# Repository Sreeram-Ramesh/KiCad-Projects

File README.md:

# KiCad Projects

An archive for all my KiCad project folders for various projects I've been working on. Find more about each of these KiCad projects on their respective repos if they exist wherein I have shared about the project itself, here's a quick overview of my KiCad designs.

<br>

## Overview

Several attempts were made by me in the past to try out designing and printing PCBs for my personal high school projects. After constant yapping and getting my dad on-board for my PCB fab through JLC PCB, results were pretty bad cuz of my PCB design skills. Some pictures for context. Fast forwarding now, I understood high-school me was pretty dumb, or always that has been the case and I am living in delulu.

<br>

<p align="center">
&nbsp;

</p>

<br>

With all that being said here are some of my recent projects.

### [1. 555 ID Badge](https://www.youtube.com/playlist?list=PLEBQazB0HUyR24ckSZ5u05TZHV9khgA1O)

This project served as a great introduction for me in KiCad. I am grateful to Digikey and Shawn Hymel for their open-source project (resources below). Through this, I learned to create custom footprints, read datasheets, search for specific IC components for projects, and design according to the capabilities of the service provider.

<br>

<p align="center">
&nbsp;

</p>

<br>

### [2. Pravega - The Line Follower](https://github.com/Sreeram-Ramesh/Pravega)

Working on an agile line follower bot utilizing the PID control algorithm. This project is being developed in association with the Build Club SSN college. Looking to quickly realize it and bring it on the competitive stage.

<br>

<p align="center">
&nbsp;

</p>

<br>

### 3. Valentino

A development board, similar to the arduino, based on the ATMEGA328 chip, design brought to life on the Valentine's day. Pretty rudimentary design. Looking forward to my microcontrollers course in semester 4. Hoping to develop more on this and have my custom microcontroller board made one day. If you have got any resources you think can help me kindly let me know. Here are some specs:

- Clock Speed: 16 MHz
- Supports SPI and UART
- Can be worn as a locket
- 16 GPIO pins in total

<br>

<p align="center">
&nbsp;

</p>

<br>

## Feedback

If you have any feedback for my work, or maybe would like to thank me for any of my custom footprints that you somehow found useful, or have some useful resources, please mail it to my [email](mailto:vgpsreerama@gmail.com).

<br>

## Acknowledgements

 - [Digikey India](https://www.digikey.in/)
 - [KiCad Tutorials](https://www.youtube.com/playlist?list=PLEBQazB0HUyR24ckSZ5u05TZHV9khgA1O)
 - [Shawn Hymel](https://www.linkedin.com/in/shawnhymel/) - For being such a treat to watch and learn, have been following him since middle school, notable influence in my academic journey.
 - [PCB Manufacturing India](https://robu.in/product/online-pcb-manufacturing-service/)

<br>

## Licenses

&nbsp;

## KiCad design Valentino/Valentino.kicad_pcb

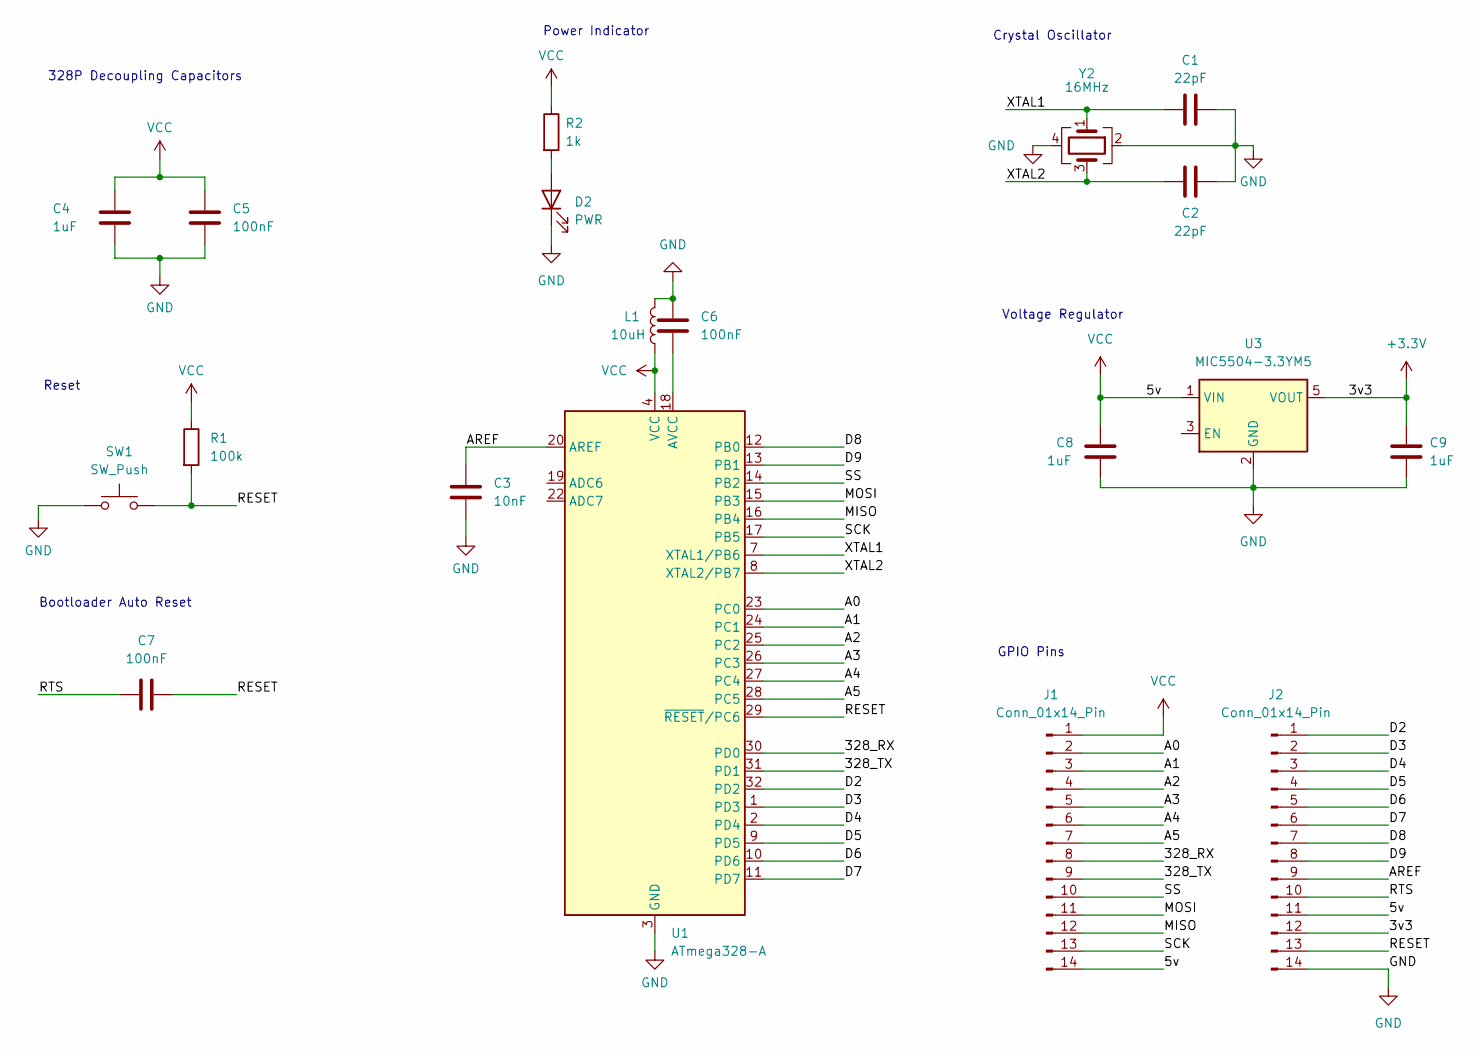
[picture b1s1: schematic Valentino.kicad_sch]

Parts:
C1, C2: 22pF; C_0805_2012Metric
C3: 10nF; C_0805_2012Metric
C4, C8, C9: 1uF; C_0805_2012Metric
C5, C6, C7: 100nF; C_0805_2012Metric
D2: PWR; LED_0805_2012Metric
J1, J2: Conn_01x14_Pin; PinHeader_1x14_P2.54mm_Vertical
L1: 10uH; L_0805_2012Metric
R1: 100k; R_0805_2012Metric
R2: 1k; R_0805_2012Metric
SW1: SW_Push; SW_SPST_PTS810
U1: ATmega328-A; TQFP-32_7x7mm_P0.8mm
U3: MIC5504-3.3YM5; SOT-23-5
Y2: 16MHz; Crystal_SMD_0603-4Pin_6.0x3.5mm

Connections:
+3.3V: C9.1, J2.12, U3.5 (VOUT)
/328_RX: J1.8, U1.30 (PD0); also elsewhere on the board
/328_TX: J1.9, U1.31 (PD1); also elsewhere on the board
/A0: J1.2, U1.23 (PC0); also elsewhere on the board
/A1: J1.3, U1.24 (PC1); also elsewhere on the board
/A2: J1.4, U1.25 (PC2); also elsewhere on the board
/A3: J1.5, U1.26 (PC3); also elsewhere on the board
/A4: J1.6, U1.27 (PC4); also elsewhere on the board
/A5: J1.7, U1.28 (PC5); also elsewhere on the board
/AREF: C3.1, J2.9, U1.20 (AREF)
/D2: J2.1, U1.32 (PD2)
/D3: J2.2, U1.1 (PD3)
/D4: J2.3, U1.2 (PD4)
/D5: J2.4, U1.9 (PD5)
/D6: J2.5, U1.10 (PD6)
/D7: J2.6, U1.11 (PD7)
/D8: J2.7, U1.12 (PB0)
/D9: J2.8, U1.13 (PB1)
/MISO: J1.12, U1.16 (PB4); also elsewhere on the board
/MOSI: J1.11, U1.15 (PB3); also elsewhere on the board
/RESET: C7.2, J2.13, R1.2, SW1.2, U1.29 (~RESET/PC6)
/RTS: C7.1, J2.10
/SCK: J1.13, U1.17 (PB5); also elsewhere on the board
/SS: J1.10, U1.14 (PB2); also elsewhere on the board
/XTAL1: C1.1, U1.7 (XTAL1/PB6), Y2.1
/XTAL2: C2.1, U1.8 (XTAL2/PB7), Y2.3
GND: C1.2, C2.2, C3.2, C4.2, C5.2, C6.1, C8.2, C9.2, D2.1 (K), J2.14, L1.2, SW1.1, U1.3 (GND), U1.5 (GND), U1.21 (GND), U3.2 (GND), Y2.2, Y2.4
unnamed: D2.2 (A), R2.2
unnamed: C6.2, U1.18 (AVCC)
VCC: C4.1, C5.1, C8.1, J1.1, J1.14, J2.11, L1.1, R1.1, R2.1, U1.4 (VCC), U1.6 (VCC), U3.1 (VIN); also elsewhere on the board

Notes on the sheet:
Bootloader Auto Reset
Power Indicator
Voltage Regulator
Reset
GPIO Pins
Crystal Oscillator
328P Decoupling Capacitors

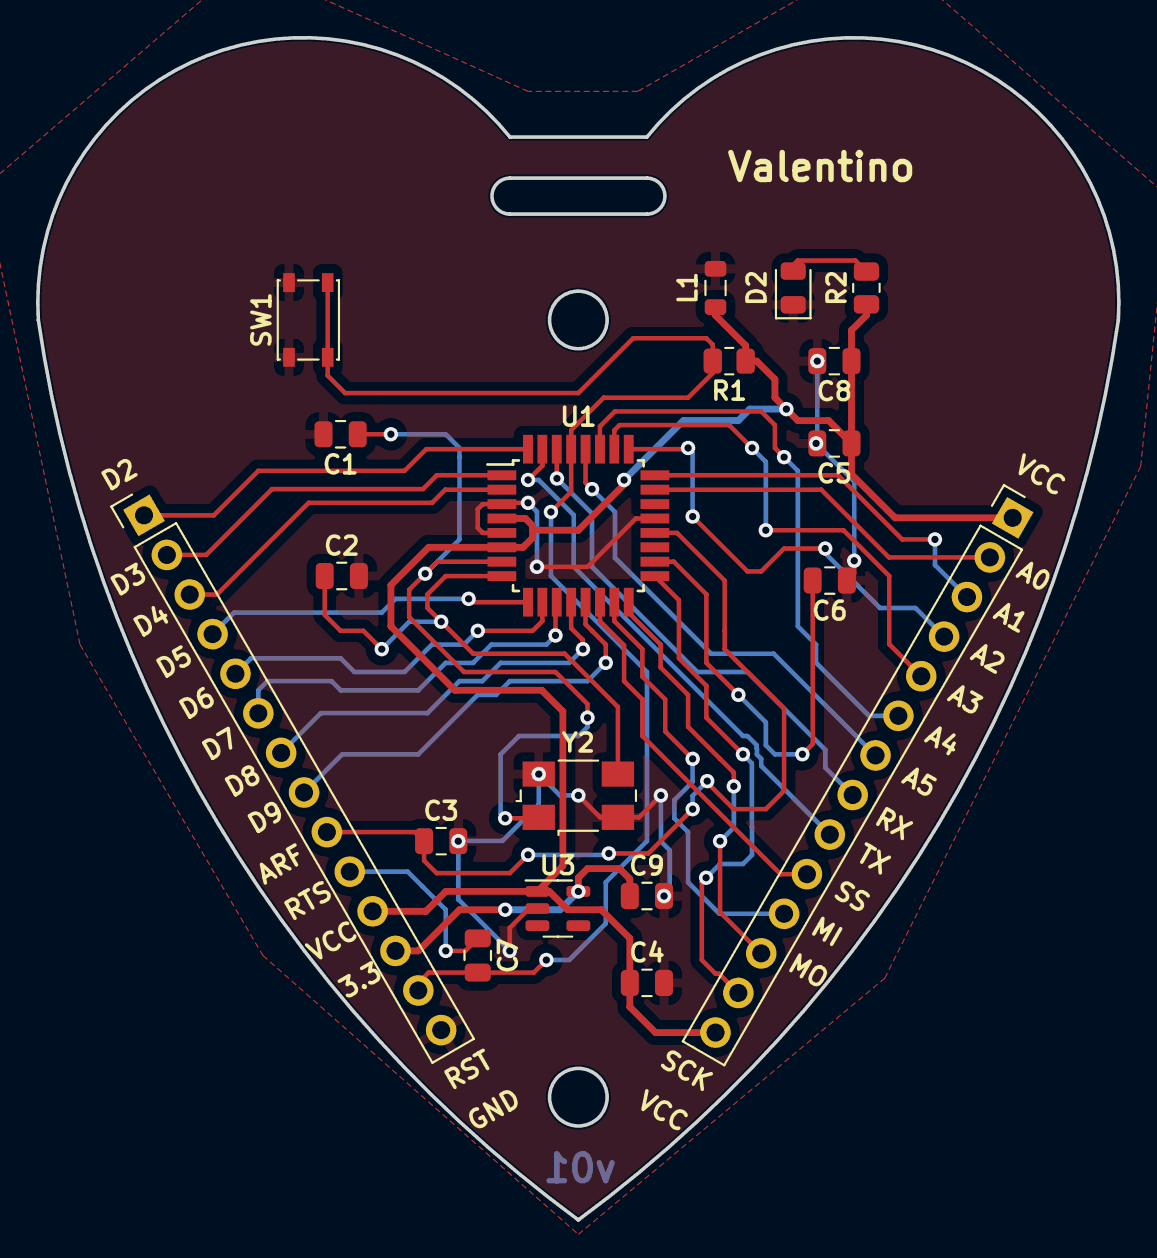
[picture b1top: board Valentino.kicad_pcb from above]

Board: 2 copper layers, 60.1 x 65.7 mm, 19 parts (0 on the bottom side), 30 nets.

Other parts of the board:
VCC: Conn_01x14_Pin; PinHeader_1x14_P2.54mm_Vertical

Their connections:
/328_RX: VCC.8; also elsewhere on the board
/328_TX: VCC.9; also elsewhere on the board
/A0: VCC.2; also elsewhere on the board
/A1: VCC.3; also elsewhere on the board
/A2: VCC.4; also elsewhere on the board
/A3: VCC.5; also elsewhere on the board
/A4: VCC.6; also elsewhere on the board
/A5: VCC.7; also elsewhere on the board
/MISO: VCC.12; also elsewhere on the board
/MOSI: VCC.11; also elsewhere on the board
/SCK: VCC.13; also elsewhere on the board
/SS: VCC.10; also elsewhere on the board
VCC: VCC.1, VCC.14; also elsewhere on the board

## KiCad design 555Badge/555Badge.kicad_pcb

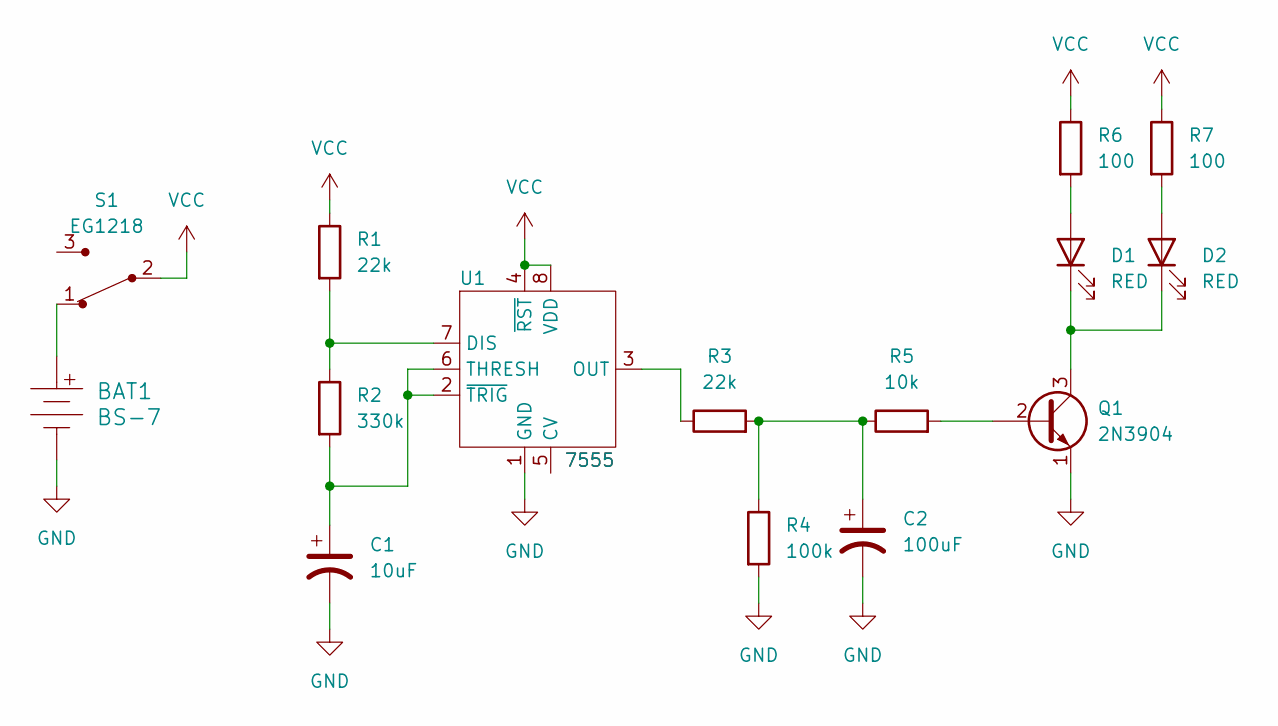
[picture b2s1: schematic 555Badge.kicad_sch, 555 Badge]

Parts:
BAT1: BS-7; Battery_Holder_Coin_2032_BS-7; MPN BS-7; Digi-Key_PN BS-7-ND
C1: 10uF; CP_Radial_D5.0mm_P2.00mm
C2: 100uF; CP_Radial_D6.3mm_P2.50mm
D1, D2: RED; LED_D3.0mm
Q1: 2N3904; TO-92-3
R1, R3: 22k; R_Axial_DIN0207_L6.3mm_D2.5mm_P7.62mm_Horizontal
R2: 330k; R_Axial_DIN0207_L6.3mm_D2.5mm_P7.62mm_Horizontal
R4: 100k; R_Axial_DIN0207_L6.3mm_D2.5mm_P7.62mm_Horizontal
R5: 10k; R_Axial_DIN0207_L6.3mm_D2.5mm_P7.62mm_Horizontal
R6, R7: 100; R_Axial_DIN0207_L6.3mm_D2.5mm_P7.62mm_Horizontal
S1: EG1218; Switch_Slide_11.6x4mm_EG1218; MPN EG1218; Digi-Key_PN EG1903-ND
U1: 7555; ICM7555-PDIP

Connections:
GND: BAT1.Neg, C1.2, C2.2, Q1.1 (E), R4.2, U1.1 (GND)
unnamed: BAT1.Pos, S1.1
unnamed: C2.1, R3.2, R4.1, R5.1
unnamed: D1.2 (A), R6.2
unnamed: D1.1 (K), D2.1 (K), Q1.3 (C)
unnamed: D2.2 (A), R7.2
unnamed: Q1.2 (B), R5.2
unnamed: R1.2, R2.1, U1.7 (DIS)
unnamed: R3.1, U1.3 (OUT)
unnamed: C1.1, R2.2, U1.2 (~TRIG), U1.6 (THRESH)
VCC: R1.1, R6.1, R7.1, S1.2, U1.4 (~RST), U1.8 (VDD)

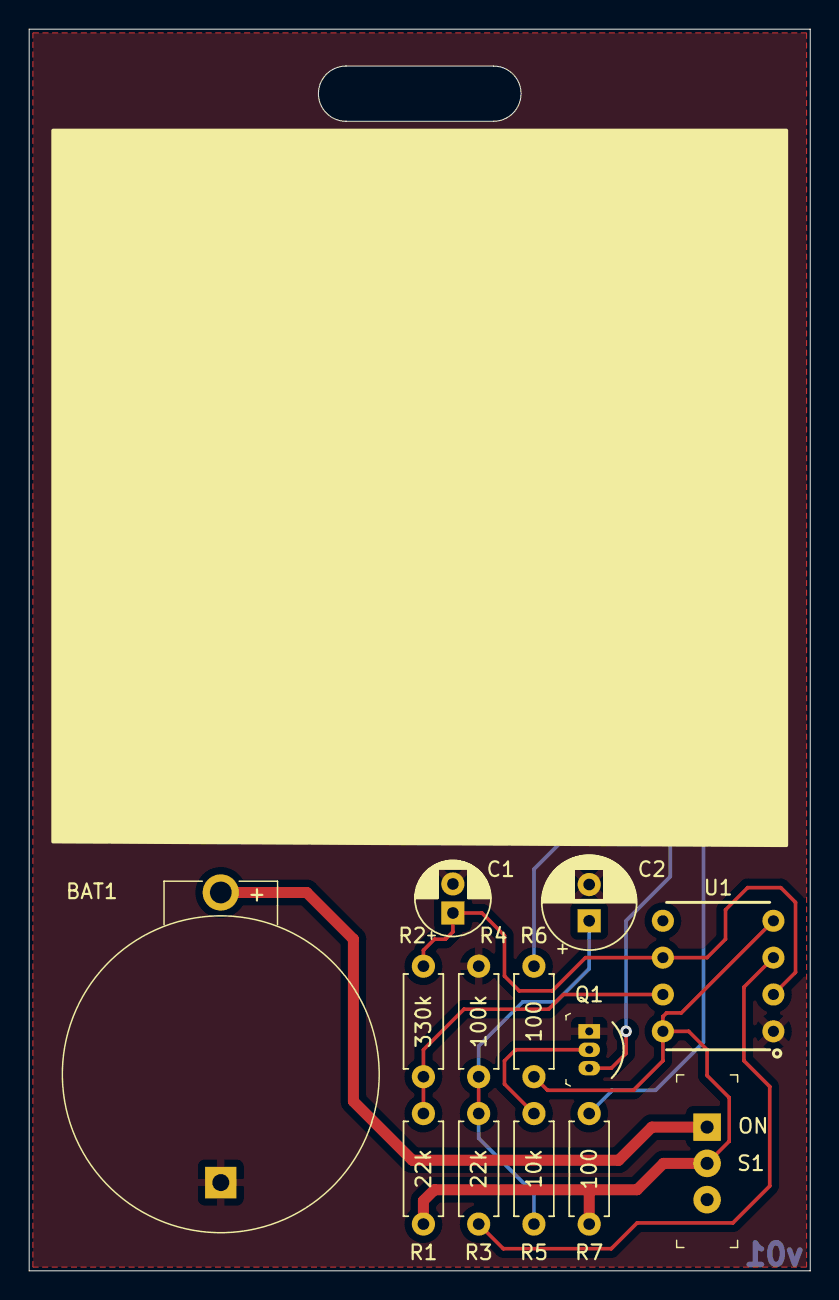
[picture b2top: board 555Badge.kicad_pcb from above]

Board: 2 copper layers, 53.8 x 85.6 mm, 15 parts (0 on the bottom side), 11 nets.

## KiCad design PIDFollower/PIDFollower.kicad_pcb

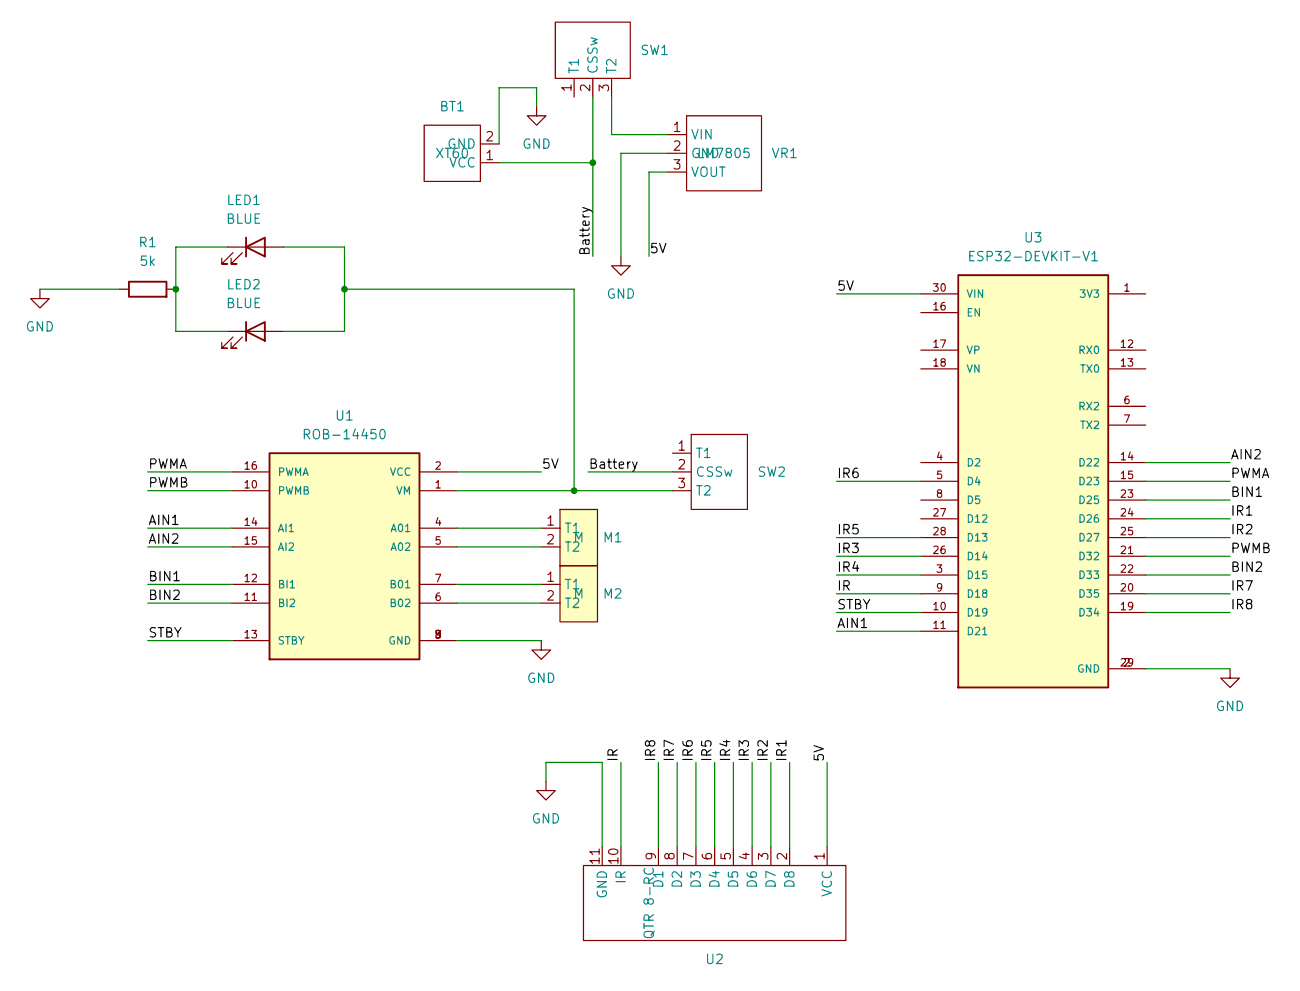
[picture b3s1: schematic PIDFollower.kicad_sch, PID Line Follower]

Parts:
BT1: XT60; TerminalBlock_bornier-2_P5.08mm
LED1, LED2: BLUE; LED_D3.0mm
M1, M2: M; TerminalBlock_bornier-2_P5.08mm
R1: 5k; R_Axial_DIN0207_L6.3mm_D2.5mm_P7.62mm_Horizontal
SW1, SW2: SSw; SW_Slide_1P2T_CK_OS102011MS2Q
U1: ROB-14450; MODULE_ROB-14450; PARTREV 11-13-17
U2: QTR 8-RC; PinHeader_1x11_P2.54mm_Vertical
U3: ESP32-DEVKIT-V1; MODULE_ESP32_DEVKIT_V1; PARTREV N/A
VR1: LM7805; PinHeader_1x03_P2.54mm_Vertical

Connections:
/5V: U1.2 (VCC), U2.1 (VCC), U3.30 (VIN), VR1.3 (VOUT)
/AIN1: U1.14 (AI1), U3.11 (D21)
/AIN2: U1.15 (AI2), U3.14 (D22)
/BIN1: U1.12 (BI1), U3.23 (D25)
/BIN2: U1.11 (BI2), U3.22 (D33)
/Battery: BT1.1 (VCC), SW1.2 (C), SW2.2 (C)
/IR: U2.10 (IR), U3.9 (D18)
/IR1: U2.2 (D8), U3.24 (D26)
/IR2: U2.3 (D7), U3.25 (D27)
/IR3: U2.4 (D6), U3.26 (D14)
/IR4: U2.5 (D5), U3.3 (D15)
/IR5: U2.6 (D4), U3.28 (D13)
/IR6: U2.7 (D3), U3.5 (D4)
/IR7: U2.8 (D2), U3.20 (D35)
/IR8: U2.9 (D1), U3.19 (D34)
/PWMA: U1.16 (PWMA), U3.15 (D23)
/PWMB: U1.10 (PWMB), U3.21 (D32)
/STBY: U1.13 (STBY), U3.10 (D19)
GND: BT1.2 (GND), R1.1, U1.3 (GND), U1.8 (GND), U1.9 (GND), U2.11 (GND), U3.2 (GND), U3.29 (GND), VR1.2 (GND)
unnamed: LED1.2 (A), LED2.2 (A), SW2.3 (T2), U1.1 (VM)
unnamed: LED1.1 (K), LED2.1 (K), R1.2
unnamed: M1.1 (T1), U1.4 (A01)
unnamed: M1.2 (T2), U1.5 (A02)
unnamed: M2.1 (T1), U1.7 (B01)
unnamed: M2.2 (T2), U1.6 (B02)
unnamed: SW1.3 (T2), VR1.1 (VIN)

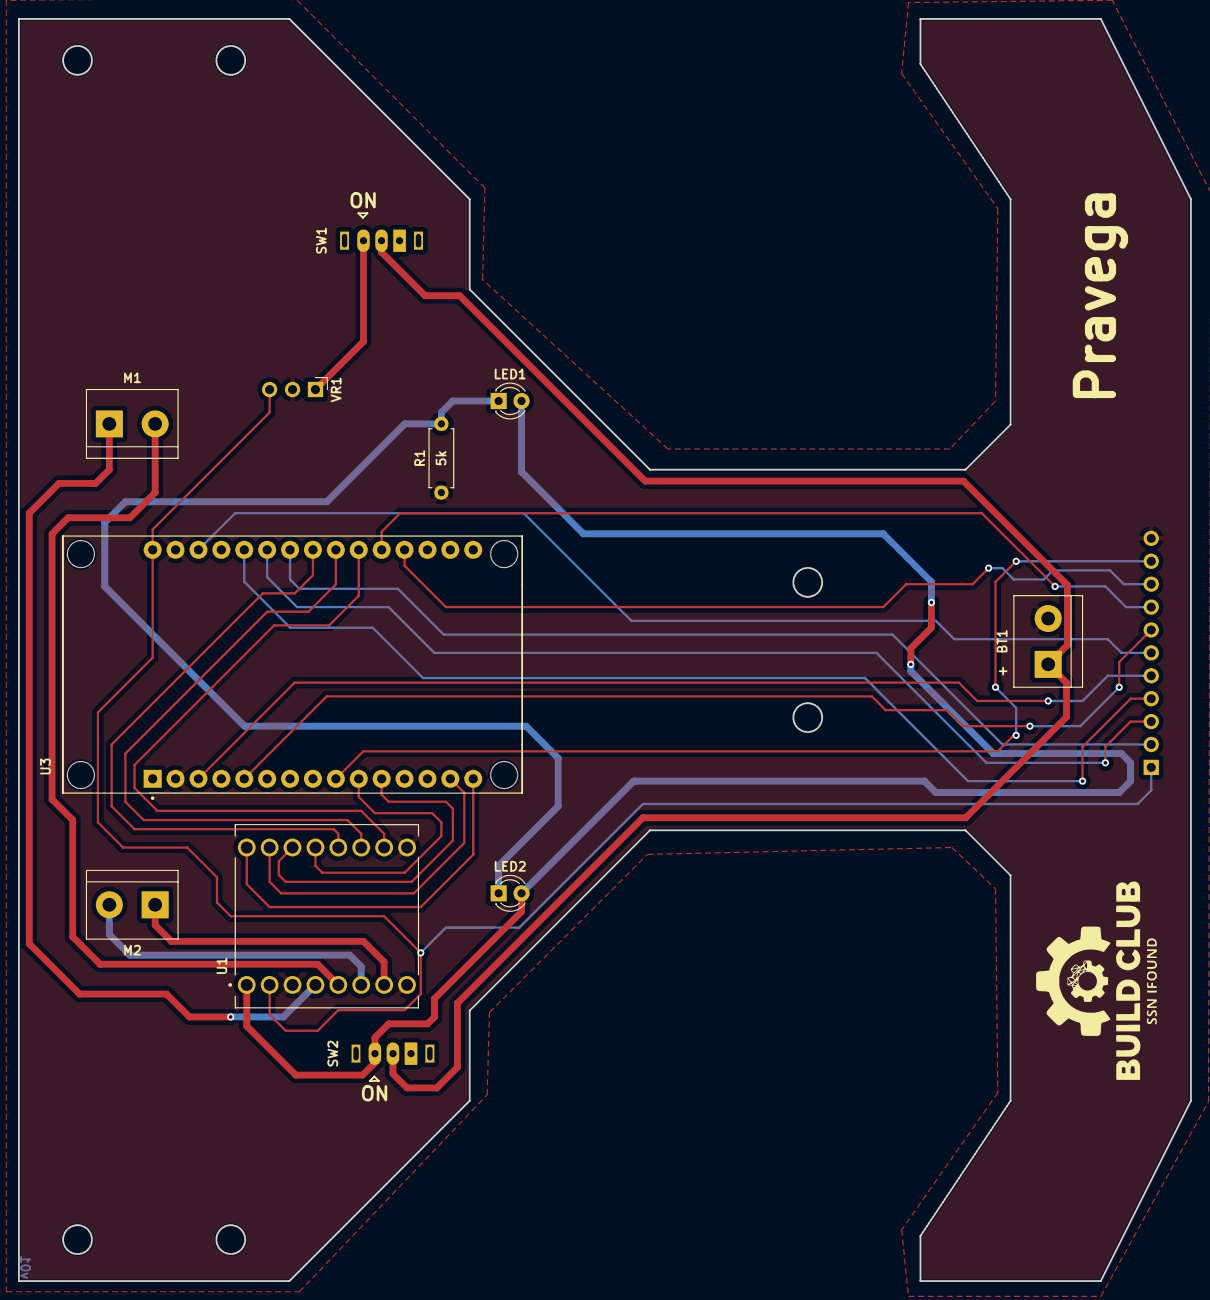
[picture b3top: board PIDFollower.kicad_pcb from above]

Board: 2 copper layers, 130.0 x 140.0 mm, 12 parts (1 on the bottom side), 26 nets.

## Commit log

2024-03-30 Added README.md file
    Revision 1
2024-06-17 Added and modified files for this repo
2024-06-17 Saved and updated README.md file
2024-06-25 Updated README.md and License

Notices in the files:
README.md:
Licenses:
[CC BY 4.0](https://creativecommons.org/licenses/by/4.0/)
[MIT License](https://choosealicense.com/licenses/mit/)
555Badge/555Badge.kicad_pcb:
License: CC by 4.0
